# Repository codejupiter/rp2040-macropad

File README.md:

# RP2040 Custom 2x2 USB Mechanical Macropad

A compact, open-hardware USB macropad built around the Raspberry Pi Pico. Four MX-compatible switches, one diode per key, and native TinyUSB HID firmware create a driverless keyboard that works on macOS, Windows, Linux, and other USB HID hosts. The included app-launcher configuration targets macOS and can be replaced with any HID shortcuts you prefer.

## At a glance

| | |
| --- | --- |
| Microcontroller | Raspberry Pi Pico / RP2040 |
| Layout | 2x2, standard 19.05 mm key pitch |
| Matrix pins | Rows: GP0, GP1 · Columns: GP6, GP7 |
| Switch isolation | Four 1N4148 diodes |
| USB | TinyUSB HID boot keyboard |
| Firmware | C++17, official Raspberry Pi Pico SDK |
| PCB | 58 x 97 mm · 2 layers · 1.6 mm FR-4 · red solder mask |
| Host software | None |

## Features

- Four independently programmable mechanical keys
- Diode-isolated matrix with debounced multi-key input
- Standard USB keyboard reports—no driver or background application
- Pico unique-ID-based USB serial number
- USB remote wake when the host permits it
- Project-local TinyUSB configuration propagated correctly through CMake
- USB stdio disabled to prevent a second device stack from colliding with HID
- One-command build and automatic `picotool`/BOOTSEL flashing
- Editable KiCad source, clean design exports, and ready-to-order fabrication files
- Automated firmware build on every push and pull request

## Design

<table>
  <tr>
    <td width="50%" align="center"><strong>Schematic</strong></td>
    <td width="50%" align="center"><strong>Routed PCB</strong></td>
  </tr>
  <tr>
    <td></td>
    <td></td>
  </tr>
</table>

The columns are inputs with the Pico's internal pull-ups enabled. During a scan, the firmware drives one row low, samples both columns, then returns that row to high impedance before selecting the next row.

```text
COL0 ── SW1 ── A D1 K ── ROW0
COL1 ── SW2 ── A D2 K ── ROW0
COL0 ── SW3 ── A D3 K ── ROW1
COL1 ── SW4 ── A D4 K ── ROW1
```

The diode cathode—the end marked by the stripe—faces the row net. The PCB silkscreen marks that pad with `K`.

### Exploded mechanical assembly

The printable [bottom enclosure and switch plate](hardware/mechanical/) are generated parametrically from the committed KiCad board outline, footprint drills, switch centers, Pico envelope, and M2 mounting holes. The animation shows the correct bottom-to-top stack and uses cyan guides for the shared mounting axes. The four keys are 1u and therefore use no stabilizers.

### Pin map

| Matrix net | Pico GPIO | Pico physical pin | Keys |
| --- | ---: | ---: | --- |
| `ROW0` | GP0 | 1 | SW1, SW2 |
| `ROW1` | GP1 | 2 | SW3, SW4 |
| `COL0` | GP6 | 9 | SW1, SW3 |
| `COL1` | GP7 | 10 | SW2, SW4 |

> **Pico orientation:** viewed from the populated side with the switches at the top, the Pico USB connector points toward the switches and the PCB's `USB Cable` label. The `A1` reference is at the opposite end. Installing the Pico 180° backward preserves USB operation but maps the PCB traces to the wrong physical pins, so none of the keys will scan.

## Repository layout

```text
.
├── CMakeLists.txt              Firmware build definition
├── main.cpp                    Matrix scanner and USB HID device
├── tusb_config.h               TinyUSB device configuration
├── flash_macropad.sh           Automatic flashing watcher
├── hardware/
│   ├── MacroPad.kicad_pro      KiCad project
│   ├── MacroPad.kicad_sch      Schematic source
│   ├── MacroPad.kicad_pcb      PCB source
│   ├── BOM.csv                 Bill of materials
│   ├── mechanical/             Parametric case, plate, STL/STEP files, and generator
│   ├── manufacturing/          Ready-to-order Gerber/drill package
│   └── reports/                ERC and DRC reports
└── docs/
    ├── ASSEMBLY.md             Assembly and bring-up guide
    └── images/                 Generated design visuals
```

## Bill of materials

| Qty. | Reference | Part | Notes |
| ---: | --- | --- | --- |
| 1 | A1 | Raspberry Pi Pico | Original Pico form factor, RP2040 |
| 4 | SW1–SW4 | MX-compatible switch | PCB-mount or plate-mount |
| 4 | D1–D4 | 1N4148 diode | DO-35, 7.62 mm pitch |
| 4 | — | 1u keycap | Any MX-compatible profile |
| 2 | — | 1x20, 2.54 mm male header | Pico connections |
| 2 | — | 1x20, 2.54 mm socket | Optional; makes the Pico removable |
| 4 | H1–H4 | M2 screw and standoff | Optional case/baseplate mounting |
| 1 | — | USB data cable | Micro-USB for the original Pico |

The machine-readable version is in [`hardware/BOM.csv`](hardware/BOM.csv).

## Build the firmware

### Requirements

- CMake 3.13 or newer
- Ninja or Make
- Arm GNU Toolchain for `arm-none-eabi`
- Official [Raspberry Pi Pico C/C++ SDK](https://github.com/raspberrypi/pico-sdk) with submodules

```bash
git clone https://github.com/codejupiter/rp2040-macropad.git
cd rp2040-macropad

export PICO_SDK_PATH=/absolute/path/to/pico-sdk
cmake -S . -B build -DCMAKE_BUILD_TYPE=Release
cmake --build build --parallel
```

The flashable image is written to `build/macropad.uf2`. The build also emits ELF, BIN, HEX, disassembly, and linker-map files for debugging.

### Default app shortcuts

The included firmware turns the physical 2x2 grid into a macOS application launcher:

| Key | Position | Action |
| --- | --- | --- |
| SW1 | Top left | Open KiCad with Spotlight |
| SW2 | Top right | Open VS Code for the Web (`vscode.dev`) in Chrome |
| SW3 | Bottom left | Open `github.com/codejupiter` in Chrome |
| SW4 | Bottom right | Open the ChatGPT/Codex desktop app with Spotlight |

SW1 and SW4 send Command+Space, type the installed application name, and press Enter. SW2 and SW3 launch Google Chrome, focus the address bar, and enter their URLs. Spotlight must use its standard Command+Space shortcut and the applications must be installed under searchable names. Presses made while another macro is running are queued and played in grid order. The Pico's onboard LED flashes three times at startup and remains lit while a debounced switch is held, separating firmware/LED failures from matrix wiring failures.

To customize the actions, edit `kKicadMacro`, `kVsCodeMacro`, `kGitHubMacro`, and `kCodexMacro` in [`main.cpp`](main.cpp), then rebuild and flash. The non-blocking macro engine supports key taps with modifiers, text entry, and timed delays. Because the device sends standard USB HID keyboard reports, no host-side driver or background utility is required.

> The example USB VID/PID is suitable for development, not for a commercial product. Obtain an appropriate allocation before distributing hardware at scale.

## Flash the Pico

The included watcher waits for a Pico, prefers a USB-capable `picotool`, and falls back to copying the UF2 to a mounted `RPI-RP2` or `RP2350` BOOTSEL volume.

```bash
./flash_macropad.sh
```

If the Pico is not detected automatically, unplug it, hold **BOOTSEL**, reconnect USB, then release the button. You can also pass a different UF2 explicitly:

```bash
./flash_macropad.sh /path/to/firmware.uf2
```

After flashing, the Pico reboots and enumerates as `RP2040 2x2 Macropad`. See the [assembly and bring-up guide](docs/ASSEMBLY.md) for first-power checks.

## Manufacture the PCB

The ready-to-upload archive is [`hardware/manufacturing/macropad_gerbers.zip`](hardware/manufacturing/macropad_gerbers.zip). It contains both copper layers, both mask layers, both silkscreen layers, the board outline, and separate plated/non-plated drill files.

Before ordering, open the archive in your manufacturer's Gerber viewer and confirm:

- 58 x 97 mm finished dimensions
- two copper layers and 1.6 mm FR-4
- red solder mask and white silkscreen
- plated Pico/switch/diode holes and non-plated M2 holes
- correct diode polarity and accessible Pico USB connector

Source and fabrication details are documented in [`hardware/README.md`](hardware/README.md).

## Validation status

- Firmware: clean release build with Pico SDK 2.3.1
- Schematic ERC: 0 errors, 0 warnings
- PCB DRC: 0 shorts, 0 clearance errors, 0 unrouted connections
- Fabrication archive: integrity checked; 9 Gerber/drill files

The stored DRC report includes library-difference advisories caused by intentionally edited reference/value text positions. They do not represent electrical or manufacturing errors.

## Contributing

Contributions are welcome. Please read [`CONTRIBUTING.md`](CONTRIBUTING.md) before opening an issue or pull request. Hardware changes should include updated KiCad sources, regenerated exports, fresh ERC/DRC reports, and inspected manufacturing outputs.

## License

Firmware, scripts, and documentation are released under the [MIT License](LICENSES/MIT.txt). Hardware design sources and fabrication files are released under the [CERN Open Hardware Licence Version 2 – Permissive](LICENSES/CERN-OHL-P-2.0.txt). See [`LICENSE`](LICENSE) for the scope of each license.

---

Built for experimentation, repeatable hardware iteration, and a satisfyingly small number of very clicky buttons.

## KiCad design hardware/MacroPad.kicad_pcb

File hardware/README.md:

# Hardware

This directory contains the editable KiCad 10 source for the 58 x 97 mm, two-layer macropad PCB.

## Files

- `MacroPad.kicad_pro` — KiCad project settings
- `MacroPad.kicad_sch` — electrical schematic
- `MacroPad.kicad_pcb` — routed PCB and board outline
- `BOM.csv` — machine-readable bill of materials
- `manufacturing/macropad_gerbers.zip` — manufacturer-ready fabrication archive
- `reports/` — saved electrical-rule and design-rule results

The local symbol and footprint tables use KiCad's `KICAD10_SYMBOL_DIR` and `KICAD10_FOOTPRINT_DIR` variables, so the project does not depend on a machine-specific application path.

## Electrical conventions

| Net | Pico pin | Function |
| --- | --- | --- |
| `ROW0` | GP0 / physical pin 1 | Driven low while scanning SW1 and SW2 |
| `ROW1` | GP1 / physical pin 2 | Driven low while scanning SW3 and SW4 |
| `COL0` | GP6 / physical pin 9 | Pulled-up input for SW1 and SW3 |
| `COL1` | GP7 / physical pin 10 | Pulled-up input for SW2 and SW4 |

Every switch connects from a column to a diode anode. Every diode cathode connects to its row. The cathode is the striped end of a physical 1N4148 and is marked `K` on the silkscreen.

## Fabrication defaults

- 58 x 97 mm finished size
- 2 layers
- 1.6 mm FR-4
- 1 oz copper
- Red solder mask
- White silkscreen

Inspect the Gerber archive with the board house viewer before checkout. The ZIP intentionally contains only fabrication files; editable source remains here in the repository.

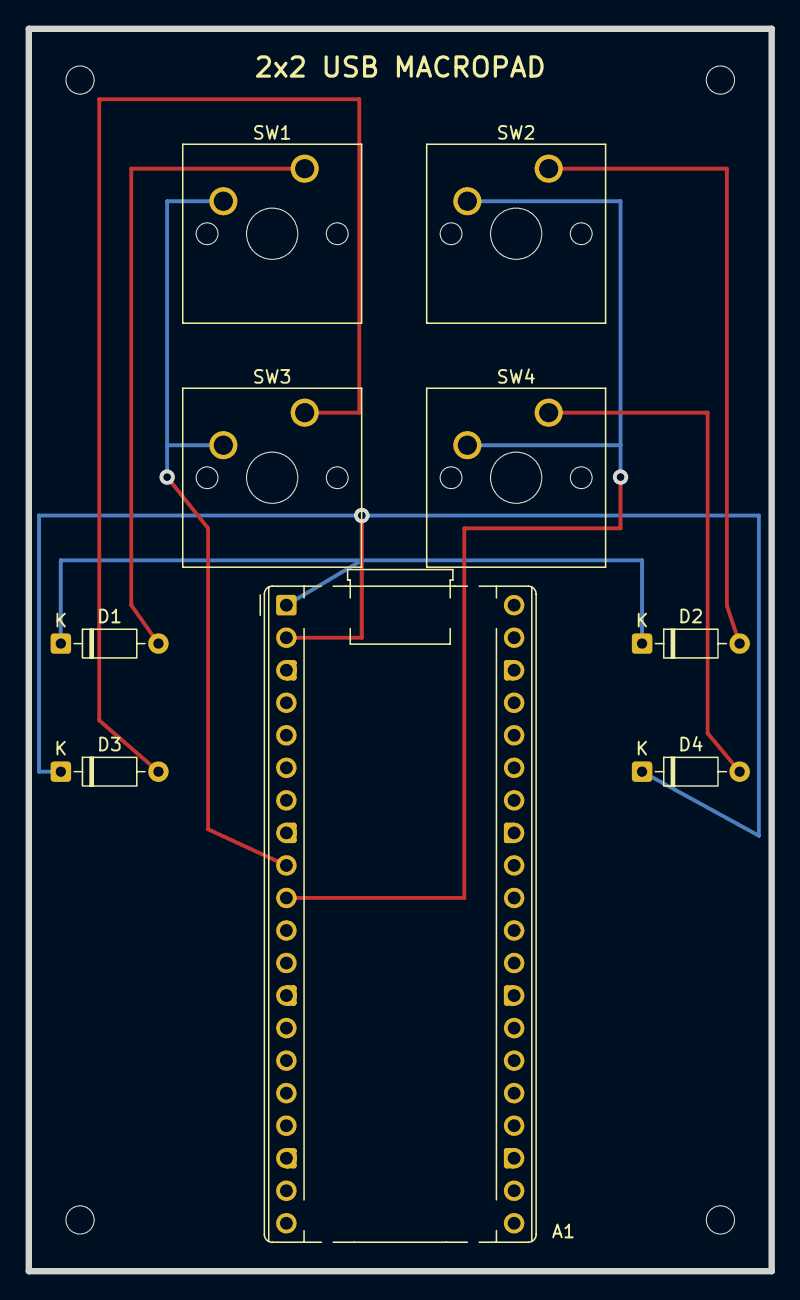
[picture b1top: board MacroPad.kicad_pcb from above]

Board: 2 copper layers, 58.0 x 97.0 mm, 13 parts (0 on the bottom side), 8 nets.

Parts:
A1: RaspberryPi_Pico; RaspberryPi_Pico_Common_THT
D1, D2, D3, D4: 1N4148; D_DO-35_SOD27_P7.62mm_Horizontal
H1, H2, H3, H4: MountingHole_2.2mm_M2
SW1: K00; SW_Cherry_MX_1.00u_PCB
SW2: K01; SW_Cherry_MX_1.00u_PCB
SW3: K10; SW_Cherry_MX_1.00u_PCB
SW4: K11; SW_Cherry_MX_1.00u_PCB

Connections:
/COL0: A1.9 (GPIO6), SW1.2, SW3.2
/COL1: A1.10 (GPIO7), SW2.2, SW4.2
/ROW0: A1.1 (GPIO0), D1.1 (K), D2.1 (K)
/ROW1: A1.2 (GPIO1), D3.1 (K), D4.1 (K)
unnamed: D1.2 (A), SW1.1
unnamed: D2.2 (A), SW2.1
unnamed: D3.2 (A), SW3.1
unnamed: D4.2 (A), SW4.1

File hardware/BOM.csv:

Quantity,References,Description,Footprint,Notes
1,A1,Raspberry Pi Pico RP2040,Module:RaspberryPi_Pico_Common_THT,Original Pico form factor
4,SW1 SW2 SW3 SW4,MX-compatible mechanical switch,Button_Switch_Keyboard:SW_Cherry_MX_1.00u_PCB,PCB-mount or plate-mount
4,D1 D2 D3 D4,1N4148 small-signal diode,Diode_THT:D_DO-35_SOD27_P7.62mm_Horizontal,Stripe/cathode faces K and row net
4,H1 H2 H3 H4,M2 mounting hardware,MountingHole:MountingHole_2.2mm_M2,Optional screws and standoffs
2,-,1x20 2.54 mm male header,-,Pico connections
2,-,1x20 2.54 mm socket,-,Optional for a removable Pico
4,-,1u MX-compatible keycap,-,Choose preferred profile
1,-,Micro-USB data cable,-,For original Raspberry Pi Pico
